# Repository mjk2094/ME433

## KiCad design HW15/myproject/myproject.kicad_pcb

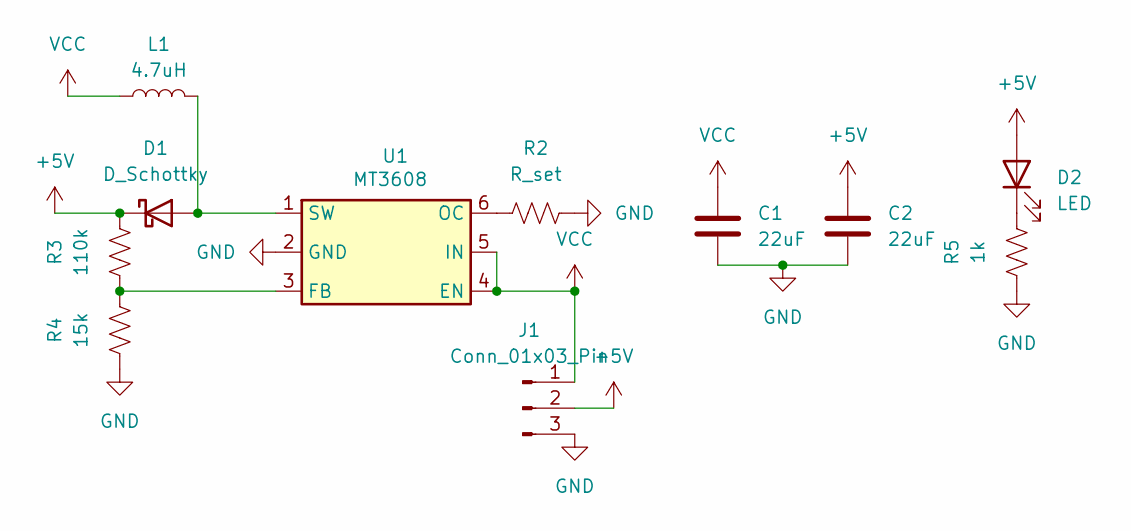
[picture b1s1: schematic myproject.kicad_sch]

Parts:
C1, C2: 22uF; C_0201_0603Metric
D1: D_Schottky; D_0201_0603Metric
D2: LED; LED_0201_0603Metric
J1: Conn_01x03_Pin; FanPinHeader_1x03_P2.54mm_Vertical
L1: 4.7uH; L_0201_0603Metric
R2: R_set; R_0201_0603Metric
R3: 110k; R_0201_0603Metric
R4: 15k; R_0201_0603Metric
R5: 1k; R_0201_0603Metric
U1: MT3608; SOT-23-6

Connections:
+5V: C2.1, D1.1 (K), D2.2 (A), J1.2, R3.2
GND: C1.2, C2.2, J1.3, R2.2, R4.1, R5.1, U1.2 (GND)
unnamed: D1.2 (A), L1.2, U1.1 (SW)
unnamed: D2.1 (K), R5.2
unnamed: R3.1, R4.2, U1.3 (FB)
unnamed: R2.1, U1.6 (OC)
VCC: C1.1, J1.1, L1.1, U1.4 (EN), U1.5 (IN)

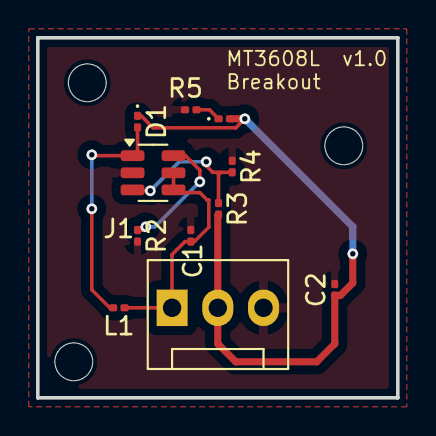
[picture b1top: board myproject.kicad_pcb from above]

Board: 2 copper layers, 20.0 x 20.0 mm, 11 parts (0 on the bottom side), 7 nets.

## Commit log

2025-04-29 hw10
2025-05-08 hw11
2025-05-14 hw13
2025-05-20 HW15
2025-05-22 hw16
2025-06-01 HW12
2025-06-01 HW17
